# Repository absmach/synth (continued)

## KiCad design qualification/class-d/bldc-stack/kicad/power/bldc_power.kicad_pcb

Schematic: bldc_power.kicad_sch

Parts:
C_3V3: 100nF; C_0603_1608Metric; Voltage 16V
C_3V3_2: 10uF; C_1206_3216Metric; Voltage 16V
C_12B2B: 100nF; C_0603_1608Metric; Voltage 25V
C_BOOT_U: 100nF; C_0603_1608Metric; Voltage 50V
C_BOOT_V: 100nF; C_0603_1608Metric; Voltage 50V
C_BOOT_W: 100nF; C_0603_1608Metric; Voltage 50V
C_BUCK_BOOT: 100nF; C_0603_1608Metric; Voltage 16V
C_BUCK_FF: 100pF; C_0603_1608Metric; Voltage 16V
C_BUCK_IN: 10uF; C_1206_3216Metric; Voltage 50V
C_BUCK_IN2: 220nF; C_0603_1608Metric; Voltage 50V
C_BUCK_OUT1, C_BUCK_OUT2: 22uF; C_1206_3216Metric; Voltage 25V
C_BUCK_OUT3: 100nF; C_0603_1608Metric; Voltage 25V
C_BULK1, C_BULK2: 470uF; CP_Radial_D12.5mm_P5.00mm; Voltage 50V; MPN EEU-FR1H471; LCSC C1589760
C_CS_U_F: 100pF; C_0603_1608Metric; Voltage 16V
C_CS_U_IN: 100nF; C_0603_1608Metric; Voltage 16V
C_CS_V_F: 100pF; C_0603_1608Metric; Voltage 16V
C_CS_V_IN: 100nF; C_0603_1608Metric; Voltage 16V
C_CS_W_F: 100pF; C_0603_1608Metric; Voltage 16V
C_CS_W_IN: 100nF; C_0603_1608Metric; Voltage 16V
C_GD_BULK: 10uF; C_1206_3216Metric; Voltage 25V
C_GD_U: 100nF; C_0603_1608Metric; Voltage 25V
C_GD_V: 100nF; C_0603_1608Metric; Voltage 25V
C_GD_W: 100nF; C_0603_1608Metric; Voltage 25V
C_IN1, C_IN2: 10uF; C_1206_3216Metric; Voltage 50V
C_IN3: 100nF; C_0603_1608Metric; Voltage 50V
C_IS_OUT_U: 100nF; C_0603_1608Metric; Voltage 16V
C_IS_OUT_V: 100nF; C_0603_1608Metric; Voltage 16V
C_IS_OUT_W: 100nF; C_0603_1608Metric; Voltage 16V
C_REF: 100nF; C_0603_1608Metric; Voltage 16V
C_VBUS_S: 100nF; C_0603_1608Metric; Voltage 16V
D_BOOT_U: 1N5819HW; D_SOD-123; MPN 1N5819HW-7-F; LCSC C82544
D_BOOT_V: 1N5819HW; D_SOD-123; MPN 1N5819HW-7-F; LCSC C82544
D_BOOT_W: 1N5819HW; D_SOD-123; MPN 1N5819HW-7-F; LCSC C82544
D_REV_Z: 15V; D_SOD-123; MPN BZT52C15; LCSC C2104
D_TVS: SMBJ30A; D_SMB; MPN SMBJ30A
H1, H2, H3, H4: (no value); MountingHole_2.5mm
J_B2B: PWR; PinSocket_2x10_P2.54mm_Vertical; MPN 2.54-2*10P; LCSC C30867
J_MOTOR: MOTOR; TerminalBlock_Phoenix_MKDS-1,5-3-5.08_1x03_P5.08mm_Horizont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; MPN 1715734; LCSC C480520
J_PWR: 24V_IN; TerminalBlock_Phoenix_MKDS-1,5-2-5.08_1x02_P5.08mm_Horizont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; MPN 1715721; LCSC C480516
L_12B2B: 600ohm@100MHz; L_0603_1608Metric
L_BUCK: 6.8uH; L_Bourns_SRN6045TA; MPN SRN6045TA-6R8M
Q_FAULT: 2N3904; TO-92_Inline; MPN 2N3904; LCSC C20505
Q_GE: IRF4905; TO-220-3_Vertical; MPN IRF4905PBF; LCSC C2564
Q_GE_CTRL: 2N3904; TO-92_Inline; MPN 2N3904; LCSC C20505
Q_REV: IRF4905; TO-220-3_Vertical; MPN IRF4905PBF; LCSC C2564
Q_UH: 80V 100A; TDSON-8-1; MPN BSC030N08NS5ATMA1; LCSC C501507
Q_UL: 80V 100A; TDSON-8-1; MPN BSC030N08NS5ATMA1; LCSC C501507
Q_VH: 80V 100A; TDSON-8-1; MPN BSC030N08NS5ATMA1; LCSC C501507
Q_VL: 80V 100A; TDSON-8-1; MPN BSC030N08NS5ATMA1; LCSC C501507
Q_WH: 80V 100A; TDSON-8-1; MPN BSC030N08NS5ATMA1; LCSC C501507
Q_WL: 80V 100A; TDSON-8-1; MPN BSC030N08NS5ATMA1; LCSC C501507
R_BUCK_FB_B: 10k; R_0603_1608Metric; Tolerance 1%
R_BUCK_FB_T: 110k; R_0603_1608Metric; Tolerance 1%
R_BUCK_RT: 33k; R_0603_1608Metric; Tolerance 1%
R_CS_U_F: 39k; R_0603_1608Metric; Tolerance 1%
R_CS_U_G: 1k; R_0603_1608Metric; Tolerance 1%
R_CS_U_IN: 1k; R_0603_1608Metric; Tolerance 1%
R_CS_V_F: 39k; R_0603_1608Metric; Tolerance 1%
R_CS_V_G: 1k; R_0603_1608Metric; Tolerance 1%
R_CS_V_IN: 1k; R_0603_1608Metric; Tolerance 1%
R_CS_W_F: 39k; R_0603_1608Metric; Tolerance 1%
R_CS_W_G: 1k; R_0603_1608Metric; Tolerance 1%
R_CS_W_IN: 1k; R_0603_1608Metric; Tolerance 1%
R_FAULT_B: 10k; R_0603_1608Metric
R_FAULT_PU: 10k; R_0603_1608Metric
R_FAULT_SENSE: 1k; R_0603_1608Metric
R_GE_B: 10k; R_0603_1608Metric
R_GE_BD: 10k; R_0603_1608Metric
R_GE_PU: 10k; R_0603_1608Metric
R_GH_U: 10R; R_0603_1608Metric
R_GH_V: 10R; R_0603_1608Metric
R_GH_W: 10R; R_0603_1608Metric
R_GL_U: 10R; R_0603_1608Metric
R_GL_V: 10R; R_0603_1608Metric
R_GL_W: 10R; R_0603_1608Metric
R_GS_UH: 10k; R_0603_1608Metric
R_GS_UL: 10k; R_0603_1608Metric
R_GS_VH: 10k; R_0603_1608Metric
R_GS_VL: 10k; R_0603_1608Metric
R_GS_WH: 10k; R_0603_1608Metric
R_GS_WL: 10k; R_0603_1608Metric
R_HIN_U: 10k; R_0603_1608Metric
R_HIN_V: 10k; R_0603_1608Metric
R_HIN_W: 10k; R_0603_1608Metric
R_IS_OUT_U: 1k; R_0603_1608Metric
R_IS_OUT_V: 1k; R_0603_1608Metric
R_IS_OUT_W: 1k; R_0603_1608Metric
R_LIN_U: 10k; R_0603_1608Metric
R_LIN_V: 10k; R_0603_1608Metric
R_LIN_W: 10k; R_0603_1608Metric
R_REF_B: 10k; R_0603_1608Metric; Tolerance 1%
R_REF_T: 10k; R_0603_1608Metric; Tolerance 1%
R_REV_G1: 22k; R_0603_1608Metric
R_REV_G2: 10k; R_0603_1608Metric
R_SH_U: 5mR; R_2512_6332Metric; Tolerance 1%
R_SH_V: 5mR; R_2512_6332Metric; Tolerance 1%
R_SH_W: 5mR; R_2512_6332Metric; Tolerance 1%
R_VBUS_S1: 100k; R_0603_1608Metric; Tolerance 1%
R_VBUS_S2: 13k; R_0603_1608Metric; Tolerance 1%
U_BUCK: LMR38010; HSOP-8-1EP_3.9x4.9mm_P1.27mm_EP2.41x3.1mm; MPN LMR38010SDDAR
U_CS1, U_CS2: MCP6022; SOIC-8_3.9x4.9mm_P1.27mm; MPN MCP6022-I/SN; LCSC C34047
U_GD_U: IR2101; SOIC-8_3.9x4.9mm_P1.27mm; MPN IR2101STRPBF; LCSC C2956
U_GD_V: IR2101; SOIC-8_3.9x4.9mm_P1.27mm; MPN IR2101STRPBF; LCSC C2956
U_GD_W: IR2101; SOIC-8_3.9x4.9mm_P1.27mm; MPN IR2101STRPBF; LCSC C2956

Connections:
+3V3: C_3V3.1, C_3V3_2.1, J_B2B.13, R_FAULT_PU.1, R_REF_T.1, U_CS1.8 (V+), U_CS2.8 (V+)
+12V: C_BUCK_FF.1, C_BUCK_OUT1.1, C_BUCK_OUT2.1, C_BUCK_OUT3.1, L_12B2B.1, L_BUCK.2, Q_GE.3 (S), R_BUCK_FB_T.1, R_GE_PU.1
+12V_B2B: C_12B2B.1, J_B2B.14, L_12B2B.2
+12V_GD: C_GD_BULK.1, C_GD_U.1, C_GD_V.1, C_GD_W.1, D_BOOT_U.2 (A), D_BOOT_V.2 (A), D_BOOT_W.2 (A), Q_GE.2 (D), U_GD_U.1 (VCC), U_GD_V.1 (VCC), U_GD_W.1 (VCC)
+24V_IN: J_PWR.1, Q_REV.2 (D)
BOOT_BUCK: C_BUCK_BOOT.1, U_BUCK.7 (boot)
BOOT_U: C_BOOT_U.1, D_BOOT_U.1 (K), U_GD_U.8 (VB)
BOOT_V: C_BOOT_V.1, D_BOOT_V.1 (K), U_GD_V.8 (VB)
BOOT_W: C_BOOT_W.1, D_BOOT_W.1 (K), U_GD_W.8 (VB)
CS_U_FB: C_CS_U_F.2, R_CS_U_F.2, R_CS_U_G.1, U_CS1.2 (-)
CS_U_IN: C_CS_U_IN.1, R_CS_U_IN.2, U_CS1.3 (+)
CS_U_OUT: C_CS_U_F.1, R_CS_U_F.1, R_IS_OUT_U.1, U_CS1.1
CS_V_FB: C_CS_V_F.2, R_CS_V_F.2, R_CS_V_G.1, U_CS1.6 (-)
CS_V_IN: C_CS_V_IN.1, R_CS_V_IN.2, U_CS1.5 (+)
CS_V_OUT: C_CS_V_F.1, R_CS_V_F.1, R_IS_OUT_V.1, U_CS1.7
CS_W_FB: C_CS_W_F.2, R_CS_W_F.2, R_CS_W_G.1, U_CS2.2 (-)
CS_W_IN: C_CS_W_IN.1, R_CS_W_IN.2, U_CS2.3 (+)
CS_W_OUT: C_CS_W_F.1, R_CS_W_F.1, R_FAULT_SENSE.1, R_IS_OUT_W.1, U_CS2.1
FAULT_DRIVE: Q_FAULT.2 (B), R_FAULT_B.1, R_FAULT_B.2, U_CS2.7
FAULT_N: J_B2B.12, Q_FAULT.3 (C), R_FAULT_PU.2
FAULT_SENSE: R_FAULT_SENSE.2, U_CS2.5 (+)
FB_BUCK: C_BUCK_FF.2, R_BUCK_FB_B.1, R_BUCK_FB_T.2, U_BUCK.5 (fb)
GATE_EN: J_B2B.11, R_GE_B.1
GATE_REV: D_REV_Z.2 (A), Q_REV.1 (G), R_REV_G1.2, R_REV_G2.1
GE_DRIVE: Q_GE_CTRL.2 (B), R_GE_B.2, R_GE_BD.1
GE_GATE: Q_GE.1 (G), Q_GE_CTRL.3 (C), R_GE_PU.2
GH_U: Q_UH.4 (G), R_GH_U.1, R_GH_U.2, R_GS_UH.1, U_GD_U.7 (HO)
GH_V: Q_VH.4 (G), R_GH_V.1, R_GH_V.2, R_GS_VH.1, U_GD_V.7 (HO)
GH_W: Q_WH.4 (G), R_GH_W.1, R_GH_W.2, R_GS_WH.1, U_GD_W.7 (HO)
GL_U: Q_UL.4 (G), R_GL_U.1, R_GL_U.2, R_GS_UL.1, U_GD_U.5 (LO)
GL_V: Q_VL.4 (G), R_GL_V.1, R_GL_V.2, R_GS_VL.1, U_GD_V.5 (LO)
GL_W: Q_WL.4 (G), R_GL_W.1, R_GL_W.2, R_GS_WL.1, U_GD_W.5 (LO)
GND: C_3V3.2, C_3V3_2.2, C_12B2B.2, C_BUCK_IN.2, C_BUCK_IN2.2, C_BUCK_OUT1.2, C_BUCK_OUT2.2, C_BUCK_OUT3.2, C_BULK1.2, C_BULK2.2, C_CS_U_IN.2, C_CS_V_IN.2, C_CS_W_IN.2, C_GD_BULK.2, C_GD_U.2, C_GD_V.2, C_GD_W.2, C_IN1.2, C_IN2.2, C_IN3.2, C_IS_OUT_U.2, C_IS_OUT_V.2, C_IS_OUT_W.2, C_REF.2, D_TVS.2 (A), J_B2B.15, J_B2B.16, J_B2B.17, J_B2B.18, J_B2B.19, J_B2B.20, J_PWR.2, Q_FAULT.1 (E), Q_GE_CTRL.1 (E), R_BUCK_FB_B.2, R_BUCK_RT.2, R_CS_U_G.2, R_CS_V_G.2, R_CS_W_G.2, R_GE_BD.2, R_HIN_U.2, R_HIN_V.2, R_HIN_W.2, R_LIN_U.2, R_LIN_V.2, R_LIN_W.2, R_REF_B.2, R_REV_G2.2, R_SH_U.2, R_SH_V.2, R_SH_W.2, U_BUCK.1 (gnd), U_BUCK.9 (pad), U_CS1.4 (V-), U_CS2.4 (V-), U_GD_U.4 (COM), U_GD_V.4 (COM), U_GD_W.4 (COM)
ISENSE_U: C_IS_OUT_U.1, J_B2B.7, R_IS_OUT_U.2
ISENSE_V: C_IS_OUT_V.1, J_B2B.8, R_IS_OUT_V.2
ISENSE_W: C_IS_OUT_W.1, J_B2B.9, R_IS_OUT_W.2
PHASE_U: C_BOOT_U.2, J_MOTOR.1, Q_UH.1 (S), Q_UH.2 (S), Q_UH.3 (S), Q_UL.5 (D), R_GS_UH.2, U_GD_U.6 (VS)
PHASE_V: C_BOOT_V.2, J_MOTOR.2, Q_VH.1 (S), Q_VH.2 (S), Q_VH.3 (S), Q_VL.5 (D), R_GS_VH.2, U_GD_V.6 (VS)
PHASE_W: C_BOOT_W.2, J_MOTOR.3, Q_WH.1 (S), Q_WH.2 (S), Q_WH.3 (S), Q_WL.5 (D), R_GS_WH.2, U_GD_W.6 (VS)
PWM_UH: J_B2B.1, R_HIN_U.1, U_GD_U.2 (HIN)
PWM_UL: J_B2B.2, R_LIN_U.1, U_GD_U.3 (LIN)
PWM_VH: J_B2B.3, R_HIN_V.1, U_GD_V.2 (HIN)
PWM_VL: J_B2B.4, R_LIN_V.1, U_GD_V.3 (LIN)
PWM_WH: J_B2B.5, R_HIN_W.1, U_GD_W.2 (HIN)
PWM_WL: J_B2B.6, R_LIN_W.1, U_GD_W.3 (LIN)
RT_BUCK: R_BUCK_RT.1, U_BUCK.4 (rt_sync)
SHUNT_U: Q_UL.1 (S), Q_UL.2 (S), Q_UL.3 (S), R_CS_U_IN.1, R_GS_UL.2, R_SH_U.1
SHUNT_V: Q_VL.1 (S), Q_VL.2 (S), Q_VL.3 (S), R_CS_V_IN.1, R_GS_VL.2, R_SH_V.1
SHUNT_W: Q_WL.1 (S), Q_WL.2 (S), Q_WL.3 (S), R_CS_W_IN.1, R_GS_WL.2, R_SH_W.1
SW_BUCK: C_BUCK_BOOT.2, L_BUCK.1, U_BUCK.8 (sw)
VBUS: C_BUCK_IN.1, C_BUCK_IN2.1, C_BULK1.1, C_BULK2.1, C_IN1.1, C_IN2.1, C_IN3.1, D_REV_Z.1 (K), D_TVS.1 (K), Q_REV.3 (S), Q_UH.5 (D), Q_VH.5 (D), Q_WH.5 (D), R_REV_G1.1, R_VBUS_S1.1, U_BUCK.2 (en), U_BUCK.3 (vin)
VBUS_SENSE: C_VBUS_S.1, J_B2B.10, R_VBUS_S1.2, R_VBUS_S2.1
VREF: C_REF.1, R_REF_B.1, R_REF_T.2, U_CS2.6 (-)

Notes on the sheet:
MOUNTING
24V INPUT
3-PHASE BRIDGE
GATE DRIVE
CURRENT SENSE
12V BUCK
BUS SENSE
OVER-CURRENT FLAG
BOARD-TO-BOARD
J_PWR 1 = +24 V, 2 = GND. Q_REV is a P-FET reverse-polarity block:
drain to input, source to VBUS. R_REV_G1/G2 22k/10k hold VGS near -16.5 V
at 24 V; D_REV_Z clamps VGS at 15 V during a TVS clamp.
D_TVS SMBJ30A: VWM 30 V, VBR 33.3-36.8 V, clamp 48.4 V at 12.4 A.
C_BULK1/2 are 470 uF 50 V (24 V x 1.5 = 36 V minimum rating).
No fuse is fitted; the 24 V feed must be externally limited to 10 A.
BSC030N08NS5: 80 V, 100 A, 3.0 mOhm max at VGS 10 V, PG-TDSON-8.
Each half bridge has three source pins in parallel; the drain pad is pin 5.
Low-side shunt 5 mOhm: 50 mV at 10 A, 0.5 W in a 2512 (1 W part).
Phase copper is 2 mm wide on 2 oz outer layers; see NETLIST.md.
IR2101: VCC 12 V, COM GND, HIN/LIN 3.3 V logic, HO/LO through 10 R.
Bootstrap: 1N5819HW from +12V_GD to VB, 100 nF from VB to VS.
HIN and LIN have 10k pulldowns so a floating MCU keeps both outputs low.
Q_GE is a 12 V load switch for the drivers, controlled by GATE_EN:
Q_GE_CTRL pulls the P-FET gate low, R_GE_PU holds it off.
IR2101 logic: HIN and LIN high together turns both outputs off;
dead time is the MCU's responsibility and is not checked by Synth.
Non-inverting gain: 1 + 39k/1k = 40. 10 A x 5 mOhm = 50 mV -> 2.0 V.
MCP6022 GBW 10 MHz, so the closed-loop band is about 250 kHz.
1k + 100 nF at the + input gives fc = 1.6 kHz; the 100 pF across
39k adds a 41 kHz pole, above the current-loop bandwidth.
The spare MCP6022 channel compares ISENSE_W with 1.65 V (about 8.25 A)
and pulls FAULT_N low through Q_FAULT.
LMR38010 (85 V absolute maximum, above the 48.4 V TVS clamp), 1 A.
Vout = 1.0 V x (1 + 110k/10k) = 12.0 V.
R_RT 33k sets 800 kHz; L 6.8 uH keeps the ripple below 0.3 A at 12 V/1 A.
L_12B2B isolates the board-to-board 12 V pin from the buck output.
VBUS divider: 24 x 13/113 = 2.76 V; 26.4 V gives 3.04 V.
This is the only 24 V signal leaving the power board.
Reference: 3.3 V x 10k/(10k+10k) = 1.65 V, about 8.25 A on the 5 mOhm shunt.
U_CS2 channel B output high on overcurrent -> Q_FAULT pulls FAULT_N low.

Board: 4 copper layers, 111 parts (0 on the bottom side), 53 nets, no tracks yet.

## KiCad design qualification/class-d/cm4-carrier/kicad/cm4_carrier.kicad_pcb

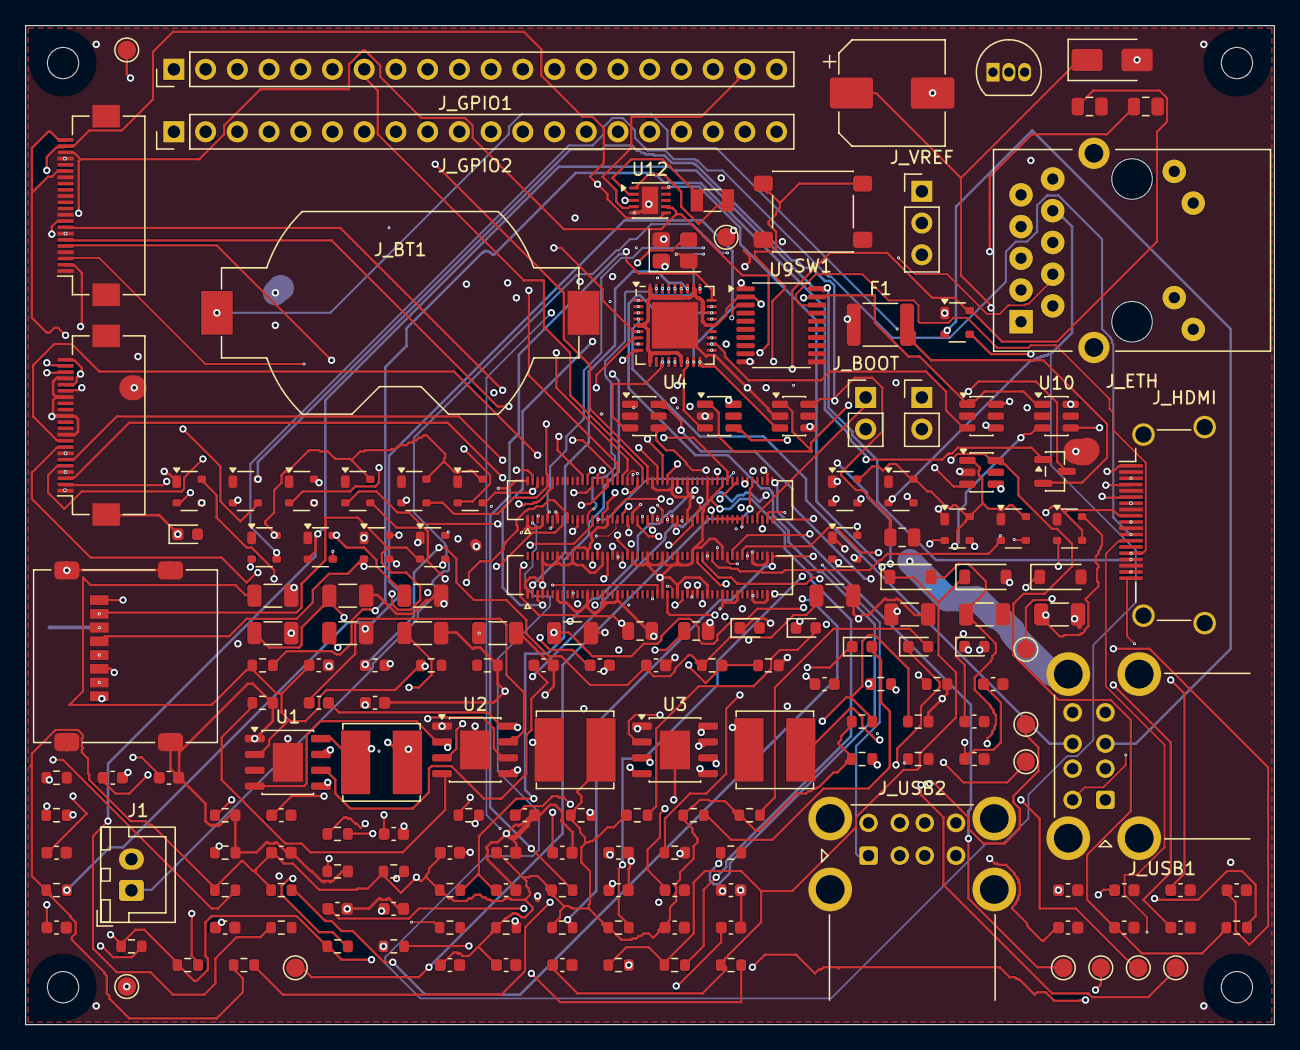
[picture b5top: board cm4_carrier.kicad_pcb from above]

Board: 6 copper layers, 100.0 x 80.0 mm, 184 parts (0 on the bottom side), 158 nets.

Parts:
C1: 47uF; CP_Elec_8x10
C2: 10uF; C_1206_3216Metric
C3: 220nF; C_0603_1608Metric
C_AUX: 10uF; C_1206_3216Metric
C_BOOT, C_BOOT2, C_BOOT3: 100nF; C_0603_1608Metric
C_CAM: 100nF; C_0603_1608Metric
C_CRFILT: 100nF; C_0603_1608Metric
C_CT1, C_CT2, C_CT3, C_CT4: 1nF; C_0603_1608Metric
C_DSI: 100nF; C_0603_1608Metric
C_FF, C_FF3: 100pF; C_0603_1608Metric
C_FF2: 56pF; C_0603_1608Metric
C_GEN: 100nF; C_0603_1608Metric
C_HDMI1: 1uF; C_0805_2012Metric
C_HDMI2: 100nF; C_0603_1608Metric
C_HDMI_CT: 1nF; C_0603_1608Metric
C_HDMI_VCCA: 100nF; C_0603_1608Metric
C_HDMI_VCCB: 100nF; C_0603_1608Metric
C_HUB1, C_HUB2, C_HUB3: 100nF; C_0603_1608Metric
C_HUB4: 10uF; C_1206_3216Metric
C_IN2_1, C_IN3_1: 10uF; C_1206_3216Metric
C_IN2_2, C_IN3_2: 220nF; C_0603_1608Metric
C_OUT1, C_OUT2, C_OUT4, C_OUT5, C_OUT7, C_OUT8: 22uF; C_1206_3216Metric
C_OUT3, C_OUT6, C_OUT9: 100nF; C_0603_1608Metric
C_PLLFILT: 100nF; C_0603_1608Metric
C_RESET: 1uF; C_0603_1608Metric
C_RTC: 100nF; C_0603_1608Metric
C_SD1: 10uF; C_1206_3216Metric
C_SD2: 100nF; C_0603_1608Metric
C_SD_CT: 1nF; C_0603_1608Metric
C_SD_IN: 100nF; C_0603_1608Metric
C_TCT: 100nF; C_0603_1608Metric
C_USB1, C_USB2, C_USB3, C_USB4: 1uF; C_0805_2012Metric
C_USB1B, C_USB2B, C_USB3B, C_USB4B: 100nF; C_0603_1608Metric
C_VCC: 1uF; C_0603_1608Metric
C_X1, C_X2: 18pF; C_0603_1608Metric
D1: SMAJ15A; D_SMA
D_3V3: 3V3; LED_0603_1608Metric
D_ACT: ACT; LED_0603_1608Metric
D_ETH: ETH_ACT; LED_0603_1608Metric
D_ETH2: ETH_SPD; LED_0603_1608Metric
D_ETH_ESD1, D_ETH_ESD2, D_ETH_ESD3, D_ETH_ESD4: TVS; SOT-143
D_FAN: FLYBACK; D_SOD-123
D_HDMI1, D_HDMI2, D_HDMI3, D_HDMI4, D_HDMI5: TVS; SOT-143
D_PWR: 5V; LED_0603_1608Metric
D_PWR_CM4: PWR; LED_0603_1608Metric
D_RTC1: 3V3; D_SOD-123
D_RTC2: BAT; D_SOD-123
D_SD1, D_SD2, D_SD3: TVS; SOT-143
D_USB1, D_USB2, D_USB3, D_USB4: TVS; SOT-143
D_USB_UP: TVS; SOT-143
F1: 2.6A_PTC; Fuse_1812_4532Metric
H1, H2, H3, H4: M2.5; MountingHole_2.5mm
J1: 12V_IN; JST_XH_B2B-XH-A_1x02_P2.50mm_Vertical
J_BOOT: nRPIBOOT; PinHeader_1x02_P2.54mm_Vertical
J_BT1: CR2032; BatteryHolder_Keystone_1058_1x2032
J_CAM: CSI0; Hirose_FH12-22S-0.5SH_1x22-1MP_P0.50mm_Horizontal
J_CM4A: CM4_A; Hirose_DF40C-100DS-0.4V_2x50_P0.4mm
J_CM4B: CM4_B; Hirose_DF40C-100DS-0.4V_2x50_P0.4mm
J_DSI: DSI0; Hirose_FH12-22S-0.5SH_1x22-1MP_P0.50mm_Horizontal
J_ETH: GbE; RJ45_UDE_RB1-125B8G1A
J_FAN: FAN; PinHeader_1x02_P2.54mm_Vertical
J_GPIO1: GPIO_ODD; PinHeader_1x20_P2.54mm_Vertical
J_GPIO2: GPIO_EVEN; PinHeader_1x20_P2.54mm_Vertical
J_HDMI: HDMI0; HDMI_A_Amphenol_10029449-x01xLF_Horizontal
J_SD: microSD; microSD_HC_Molex_47219-2001
J_USB1: USB1_2; USB_A_CUI_UJ2-ADH-TH_Horizontal_Stacked
J_USB2: USB3_4; USB_A_CUI_UJ2-ADH-TH_Horizontal_Stacked
J_VREF: VREF_SEL; PinHeader_1x03_P2.54mm_Vertical
L1, L2, L3: 6.8uH; L_Bourns_SRN6045TA
L_FB1: 600R; L_0603_1608Metric
Q1: DMP3098L; SOT-23
Q_LED: 2N7000; TO-92_Inline
R_3V3: 470; R_0603_1608Metric
R_ACT: 470; R_0603_1608Metric
R_CFG0, R_CFG1: 10k; R_0603_1608Metric
R_ETH, R_ETH2: 470; R_0603_1608Metric
R_FB2_B: 43.2k; R_0603_1608Metric
R_FB2_T, R_FB3_T: 100k; R_0603_1608Metric
R_FB3_B: 125k; R_0603_1608Metric
R_FB_B: 24.9k; R_0603_1608Metric
R_FB_T: 100k; R_0603_1608Metric
R_G1: 100k; R_0603_1608Metric
R_GEN: 100k; R_0603_1608Metric
R_HDMI_SCL: 2.2k; R_0603_1608Metric
R_HDMI_SCL_MCU: 2.2k; R_0603_1608Metric
R_HDMI_SDA: 2.2k; R_0603_1608Metric
R_HDMI_SDA_MCU: 2.2k; R_0603_1608Metric
R_LED_PWR: 470; R_0603_1608Metric
R_LOCAL: 10k; R_0603_1608Metric
R_OCS1, R_OCS2, R_OCS3, R_OCS4: 10k; R_0603_1608Metric
R_OE: 10k; R_0603_1608Metric
R_PG, R_PG2, R_PG3: 100k; R_0603_1608Metric
R_PWR: 470; R_0603_1608Metric
R_RBIAS: 12k; R_0603_1608Metric
R_RESET: 10k; R_0603_1608Metric
R_RT2, R_RT3: 33k; R_0603_1608Metric
R_RTC_INT: 10k; R_0603_1608Metric
R_RTC_SCL: 10k; R_0603_1608Metric
R_RTC_SDA: 10k; R_0603_1608Metric
R_SD_CMD: 10k; R_0603_1608Metric
R_SD_DAT0, R_SD_DAT1, R_SD_DAT2, R_SD_DAT3: 10k; R_0603_1608Metric
R_SD_PWR: 100k; R_0603_1608Metric
R_UV_B: 10k; R_0603_1608Metric
R_UV_T: 63.4k; R_0603_1608Metric
R_VBUS: 10k; R_0603_1608Metric
SW1: GLOBAL_EN; SW_SPST_PTS645Sx43SMTR92
TP_1V8: 1V8; TestPoint_Pad_D1.5mm
TP_3V3: 3V3; TestPoint_Pad_D1.5mm
TP_5V: 5V; TestPoint_Pad_D1.5mm
TP_CM4_1V8: CM4_1V8; TestPoint_Pad_D1.5mm
TP_CM4_3V3: CM4_3V3; TestPoint_Pad_D1.5mm
TP_GLOBAL_EN: GLOBAL_EN; TestPoint_Pad_D1.5mm
TP_NEXTRST: nEXTRST; TestPoint_Pad_D1.5mm
TP_PG1V8: PG_1V8; TestPoint_Pad_D1.5mm
TP_PG3V3: PG_3V3; TestPoint_Pad_D1.5mm
TP_PG5V: PG_5V; TestPoint_Pad_D1.5mm
TP_RUN_PG: RUN_PG; TestPoint_Pad_D1.5mm
U1: LMR33640; HSOP-8-1EP_3.9x4.9mm_P1.27mm_EP2.41x3.1mm
U2, U3: LMR38010; HSOP-8-1EP_3.9x4.9mm_P1.27mm_EP2.41x3.1mm
U4: USB2514B; QFN-36-1EP_6x6mm_P0.5mm_EP3.7x3.7mm
U5: USB1_PWR; SOT-23-6
U6: USB2_PWR; SOT-23-6
U7: USB3_PWR; SOT-23-6
U8: USB4_PWR; SOT-23-6
U9: TXS0108E; TSSOP-20_4.4x6.5mm_P0.65mm
U10: HDMI_5V; SOT-23-6
U11: SD_PWR; SOT-23-6
U12: PCF85063A; DFN-10-1EP_2.6x2.6mm_P0.5mm_EP1.3x2.2mm
Y1: 24MHz; Crystal_SMD_3225-4Pin_3.2x2.5mm
Y2: 32.768kHz; Crystal_SMD_3215-2Pin_3.2x1.5mm

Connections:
+1V8: C_OUT7.1, C_OUT8.1, C_OUT9.1, J_VREF.3, L3.2, R_FB3_T.1, R_PG3.1, TP_1V8.1
+3V3: C_CAM.1, C_DSI.1, C_HDMI_VCCA.1, C_HUB1.1, C_HUB2.1, C_HUB3.1, C_HUB4.1, C_OUT4.1, C_OUT5.1, C_OUT6.1, C_SD_IN.1, D_ETH_ESD1.4, D_ETH_ESD2.4, D_ETH_ESD3.4, D_ETH_ESD4.4, D_HDMI1.4, D_HDMI2.4, D_HDMI3.4, D_HDMI4.4, D_RTC1.2, D_USB_UP.4, J_CAM.18, J_CAM.22, J_DSI.17, J_DSI.22, J_GPIO1.1, J_GPIO1.9, J_VREF.1, L2.2, R_3V3.1, R_ACT.1, R_ETH.1, R_ETH2.1, R_FB2_T.1, R_GEN.1, R_HDMI_SCL_MCU.1, R_HDMI_SDA_MCU.1, R_LED_PWR.1, R_OCS1.1, R_OCS2.1, R_OCS3.1, R_OCS4.1, R_OE.1, R_PG2.1, R_RESET.1, R_SD_PWR.1, R_VBUS.1, TP_3V3.1, U4.5, U4.10, U4.15, U4.23, U4.29, U4.36, U9.2, U10.3, U11.1
+5V: C_HDMI_VCCB.1, C_OUT1.1, C_OUT2.1, C_OUT3.1, D_FAN.1, D_HDMI5.4, J_CM4A.77, J_CM4A.79, J_CM4A.81, J_CM4A.83, J_CM4A.85, J_CM4A.87, J_FAN.1, J_GPIO2.1, J_GPIO2.2, L1.2, L_FB1.1, R_FB_T.1, R_PG.1, R_PWR.1, TP_5V.1, U5.1, U6.1, U7.1, U8.1, U9.19, U10.1
+5V_AUX: C_AUX.1, C_IN2_1.1, C_IN2_2.1, C_IN3_1.1, C_IN3_2.1, L_FB1.2, U2.3, U3.3
BOOT_1V8: C_BOOT3.1, U3.7
BOOT_3V3: C_BOOT2.1, U2.7
BOOT_5V: C_BOOT.1, U1.7
CAM_CK_N: J_CAM.8, J_CM4B.40
CAM_CK_P: J_CAM.9, J_CM4B.42
CAM_D0_N: J_CAM.2, J_CM4B.28
CAM_D0_P: J_CAM.3, J_CM4B.30
CAM_D1_N: J_CAM.5, J_CM4B.34
CAM_D1_P: J_CAM.6, J_CM4B.36
CAM_GPIO: J_CAM.17, J_CM4A.97
CM4_1V8: J_CM4A.88, J_CM4A.90, TP_CM4_1V8.1
CM4_3V3: J_CM4A.84, J_CM4A.86, TP_CM4_3V3.1
DSI_CK_N: J_CM4B.69, J_DSI.8
DSI_CK_P: J_CM4B.71, J_DSI.9
DSI_D0_N: J_CM4B.57, J_DSI.2
DSI_D0_P: J_CM4B.59, J_DSI.3
DSI_D1_N: J_CM4B.63, J_DSI.5
DSI_D1_P: J_CM4B.65, J_DSI.6
ETH0_N: D_ETH_ESD1.3, J_CM4A.10, J_ETH.R3
ETH0_P: D_ETH_ESD1.2, J_CM4A.12, J_ETH.R2
ETH1_N: D_ETH_ESD2.3, J_CM4A.6, J_ETH.R5
ETH1_P: D_ETH_ESD2.2, J_CM4A.4, J_ETH.R4
ETH2_N: D_ETH_ESD3.3, J_CM4A.9, J_ETH.R7
ETH2_P: D_ETH_ESD3.2, J_CM4A.11, J_ETH.R6
ETH3_N: D_ETH_ESD4.3, J_CM4A.5, J_ETH.R9
ETH3_P: D_ETH_ESD4.2, J_CM4A.3, J_ETH.R8
ETH_LED_ACT: D_ETH.1, J_CM4A.15
ETH_LED_SPD: D_ETH2.1, J_CM4A.17
ETH_TCT: C_TCT.1, J_ETH.R1
FB_1V8: C_FF3.1, R_FB3_B.1, R_FB3_T.2, U3.5
FB_3V3: C_FF2.1, R_FB2_B.1, R_FB2_T.2, U2.5
FB_5V: C_FF.1, R_FB_B.1, R_FB_T.2, U1.5
GLOBAL_EN: C_GEN.1, J_CM4A.99, R_GEN.2, SW1.1, TP_GLOBAL_EN.1
GND: C1.2, C2.2, C3.2, C_AUX.2, C_CAM.2, C_CRFILT.2, C_CT1.2, C_CT2.2, C_CT3.2, C_CT4.2, C_DSI.2, C_GEN.2, C_HDMI1.2, C_HDMI2.2, C_HDMI_CT.2, C_HDMI_VCCA.2, C_HDMI_VCCB.2, C_HUB1.2, C_HUB2.2, C_HUB3.2, C_HUB4.2, C_IN2_1.2, C_IN2_2.2, C_IN3_1.2, C_IN3_2.2, C_OUT1.2, C_OUT2.2, C_OUT3.2, C_OUT4.2, C_OUT5.2, C_OUT6.2, C_OUT7.2, C_OUT8.2, C_OUT9.2, C_PLLFILT.2, C_RESET.2, C_RTC.2, C_SD1.2, C_SD2.2, C_SD_CT.2, C_SD_IN.2, C_TCT.2, C_USB1.2, C_USB1B.2, C_USB2.2, C_USB2B.2, C_USB3.2, C_USB3B.2, C_USB4.2, C_USB4B.2, C_VCC.2, C_X1.2, C_X2.2, D1.2, D_3V3.1, D_ETH_ESD1.1, D_ETH_ESD2.1, D_ETH_ESD3.1, D_ETH_ESD4.1, D_FAN.2, D_HDMI1.1, D_HDMI2.1, D_HDMI3.1, D_HDMI4.1, D_HDMI5.1, D_PWR.1, D_SD1.1, D_SD2.1, D_SD3.1, D_USB1.1, D_USB2.1, D_USB3.1, D_USB4.1, D_USB_UP.1, J1.2, J_BOOT.2, J_BT1.2, J_CAM.1, J_CAM.4, J_CAM.7, J_CAM.10, J_CAM.13, J_CAM.16, J_CAM.19, J_CAM.MP, J_CM4A.1, J_CM4A.2, J_CM4A.7, J_CM4A.8, J_CM4A.13, J_CM4A.14, J_CM4A.22, J_CM4A.23, J_CM4A.32, J_CM4A.33, J_CM4A.42, J_CM4A.43, J_CM4A.52, J_CM4A.53, J_CM4A.59, J_CM4A.60, J_CM4A.65, J_CM4A.66, J_CM4A.71, J_CM4A.74, J_CM4A.98, J_CM4B.1, J_CM4B.7, J_CM4B.8, J_CM4B.13, J_CM4B.14, J_CM4B.19, J_CM4B.20, J_CM4B.25, J_CM4B.26, J_CM4B.31, J_CM4B.32, J_CM4B.37, J_CM4B.38, J_CM4B.44, J_CM4B.50, J_CM4B.55, J_CM4B.56, J_CM4B.61, J_CM4B.62, J_CM4B.67, J_CM4B.68, J_CM4B.73, J_CM4B.74, J_CM4B.79, J_CM4B.80, J_CM4B.85, J_CM4B.86, J_CM4B.91, J_CM4B.92, J_CM4B.97, J_CM4B.98, J_DSI.1, J_DSI.4, J_DSI.7, J_DSI.10, J_DSI.13, J_DSI.16, J_DSI.19, J_DSI.MP, J_ETH.R10, J_ETH.SH, J_FAN.2, J_GPIO1.5, J_GPIO1.13, J_GPIO1.20, J_GPIO2.3, J_GPIO2.7, J_GPIO2.10, J_GPIO2.15, J_GPIO2.17, J_HDMI.2, J_HDMI.5, J_HDMI.8, J_HDMI.11, J_HDMI.17, J_HDMI.SH, J_SD.6, J_SD.SH, J_USB1.4, J_USB1.8, J_USB1.SH, J_USB2.4, J_USB2.8, J_USB2.SH, Q_LED.1, R_3V3.2, R_CFG0.2, R_CFG1.2, R_FB2_B.2, R_FB3_B.2, R_FB_B.2, R_LOCAL.2, R_PWR.2, R_RBIAS.2, R_RT2.2, R_RT3.2, R_UV_B.2, SW1.2, U1.1, U1.9, U2.1, U2.9, U3.1, U3.9, U4.37, U5.2, U6.2, U7.2, U8.2, U9.11, U10.2, U11.2, U12.5, U12.11, Y1.2, Y1.4
GPIO2: J_CM4A.58, J_GPIO1.2
GPIO3: J_CM4A.56, J_GPIO1.3
GPIO4: J_CM4A.54, J_GPIO1.4
GPIO5: J_CM4A.34, J_GPIO1.15
GPIO6: J_CM4A.30, J_GPIO1.16
GPIO7: J_CM4A.37, J_GPIO2.13
GPIO8: J_CM4A.39, J_GPIO2.12
GPIO9: J_CM4A.40, J_GPIO1.11
GPIO10: J_CM4A.44, J_GPIO1.10
GPIO11: J_CM4A.38, J_GPIO1.12
GPIO12: J_CM4A.31, J_GPIO2.16
GPIO13: J_CM4A.28, J_GPIO1.17
GPIO14: J_CM4A.55, J_GPIO2.4
GPIO15: J_CM4A.51, J_GPIO2.5
GPIO16: J_CM4A.29, J_GPIO2.18
GPIO17: J_CM4A.50, J_GPIO1.6
GPIO18: J_CM4A.49, J_GPIO2.6
GPIO19: J_CM4A.26, J_GPIO1.18
GPIO20: J_CM4A.27, J_GPIO2.19
GPIO21: J_CM4A.25, J_GPIO2.20
GPIO22: J_CM4A.46, J_GPIO1.8
GPIO23: J_CM4A.47, J_GPIO2.8
GPIO24: J_CM4A.45, J_GPIO2.9
GPIO25: J_CM4A.41, J_GPIO2.11
GPIO26: J_CM4A.24, J_GPIO1.19, R_RTC_INT.2, U12.4
GPIO27: J_CM4A.48, J_GPIO1.7
GPIO_VREF: J_CM4A.78, J_VREF.2
HDMI_5V: C_HDMI1.1, C_HDMI2.1, J_HDMI.18, U10.6
HDMI_CEC: J_CM4B.51, J_HDMI.13
HDMI_CK_N: D_HDMI4.3, J_CM4B.90, J_HDMI.12
HDMI_CK_P: D_HDMI4.2, J_CM4B.88, J_HDMI.10
HDMI_CT: C_HDMI_CT.1, U10.4
HDMI_D0_N: D_HDMI3.3, J_CM4B.84, J_HDMI.9
HDMI_D0_P: D_HDMI3.2, J_CM4B.82, J_HDMI.7
HDMI_D1_N: D_HDMI2.3, J_CM4B.78, J_HDMI.6
HDMI_D1_P: D_HDMI2.2, J_CM4B.76, J_HDMI.4
HDMI_D2_N: D_HDMI1.3, J_CM4B.72, J_HDMI.3
HDMI_D2_P: D_HDMI1.2, J_CM4B.70, J_HDMI.1
HDMI_HPD: J_CM4B.53, J_HDMI.19
HDMI_OE: R_OE.2, U9.10
HDMI_SCL_CONN: D_HDMI5.3, J_HDMI.15, R_HDMI_SCL.1, U9.18
HDMI_SCL_MCU: J_CM4B.100, R_HDMI_SCL_MCU.2, U9.3
HDMI_SDA_CONN: D_HDMI5.2, J_HDMI.16, R_HDMI_SDA.1, U9.20
HDMI_SDA_MCU: J_CM4B.99, R_HDMI_SDA_MCU.2, U9.1
HUB_CFG0: R_CFG0.1, U4.24
HUB_CFG1: R_CFG1.1, U4.25
HUB_CRFILT: C_CRFILT.1, U4.14
HUB_LOCAL: R_LOCAL.1, U4.28
HUB_OCS1: R_OCS1.2, U4.13
HUB_OCS2: R_OCS2.2, U4.17
HUB_OCS3: R_OCS3.2, U4.19
HUB_OCS4: R_OCS4.2, U4.21
HUB_PLLFILT: C_PLLFILT.1, U4.34
HUB_RBIAS: R_RBIAS.1, U4.35
HUB_RESET: C_RESET.1, R_RESET.2, U4.26
HUB_VBUS_DET: R_VBUS.2, U4.27
HUB_XTAL1: C_X1.1, U4.33, Y1.1
HUB_XTAL2: C_X2.1, U4.32, Y1.3
ID_SC: J_CM4A.35, J_GPIO2.14
ID_SD: J_CM4A.36, J_GPIO1.14
LED_ACT_A: D_ACT.2, R_ACT.2
LED_ETH2_A: D_ETH2.2, R_ETH2.2
LED_ETH_A: D_ETH.2, R_ETH.2
LED_PWR_CM4: D_PWR_CM4.1, Q_LED.3
LED_PWR_CM4_A: D_PWR_CM4.2, R_LED_PWR.2
NEXTRST: J_CM4A.100, TP_NEXTRST.1
NRPIBOOT: J_BOOT.1, J_CM4A.93
PG_1V8: R_PG3.2, TP_PG1V8.1, U3.6
PG_3V3: R_PG2.2, TP_PG3V3.1, U2.6, U3.2
PG_5V: R_PG.2, TP_PG5V.1, U1.4, U2.2
PI_LED_ACT: D_ACT.1, J_CM4A.21
PI_LED_NPWR: J_CM4A.95, Q_LED.2
RTC_BAT: D_RTC2.2, J_BT1.1
RTC_OSC1: U12.1, Y2.1
RTC_OSC2: U12.2, Y2.2
RTC_VDD: C_RTC.1, D_RTC1.1, D_RTC2.1, R_RTC_INT.1, R_RTC_SCL.1, R_RTC_SDA.1, U12.3, U12.10
RT_1V8: R_RT3.1, U3.4
RT_3V3: R_RT2.1, U2.4
RUN_PG: J_CM4A.92, TP_RUN_PG.1
SCL0: J_CAM.20, J_CM4A.80, J_DSI.20, R_RTC_SCL.2, U12.7
SDA0: J_CAM.21, J_CM4A.82, J_DSI.21, R_RTC_SDA.2, U12.6
SD_CLK: D_SD1.2, J_CM4A.57, J_SD.5
SD_CMD: D_SD1.3, J_CM4A.62, J_SD.3, R_SD_CMD.2
SD_CT: C_SD_CT.1, U11.4
SD_DAT0: D_SD2.2, J_CM4A.63, J_SD.7, R_SD_DAT0.2
SD_DAT1: D_SD2.3, J_CM4A.67, J_SD.8, R_SD_DAT1.2
SD_DAT2: D_SD3.2, J_CM4A.69, J_SD.1, R_SD_DAT2.2
SD_DAT3: D_SD3.3, J_CM4A.61, J_SD.2, R_SD_DAT3.2
SD_PWR_ON: J_CM4A.75, R_SD_PWR.2, U11.3
SD_VDD: C_SD1.1, C_SD2.1, D_SD1.4, D_SD2.4, D_SD3.4, J_SD.4, R_SD_CMD.1, R_SD_DAT0.1, R_SD_DAT1.1, R_SD_DAT2.1, R_SD_DAT3.1, U11.6
SW_1V8: C_BOOT3.2, L3.1, U3.8
SW_3V3: C_BOOT2.2, L2.1, U2.8
SW_5V: C_BOOT.2, L1.1, U1.8
USB1_N: D_USB1.3, J_USB1.2, U4.1
USB1_P: D_USB1.2, J_USB1.3, U4.2
USB2_N: D_USB2.3, J_USB1.6, U4.3
USB2_P: D_USB2.2, J_USB1.7, U4.4
USB3_N: D_USB3.3, J_USB2.2, U4.6
USB3_P: D_USB3.2, J_USB2.3, U4.7
USB4_N: D_USB4.3, J_USB2.6, U4.8
USB4_P: D_USB4.2, J_USB2.7, U4.9
USB_CT1: C_CT1.1, U5.4
USB_CT2: C_CT2.1, U6.4
USB_CT3: C_CT3.1, U7.4
USB_CT4: C_CT4.1, U8.4
USB_ON1: U4.12, U5.3
USB_ON2: U4.16, U6.3
USB_ON3: U4.18, U7.3
USB_ON4: U4.20, U8.3
USB_UP_N: D_USB_UP.3, J_CM4B.3, U4.30
USB_UP_P: D_USB_UP.2, J_CM4B.5, U4.31
USB_VBUS1: C_USB1.1, C_USB1B.1, D_USB1.4, J_USB1.1, U5.6
USB_VBUS2: C_USB2.1, C_USB2B.1, D_USB2.4, J_USB1.5, U6.6
USB_VBUS3: C_USB3.1, C_USB3B.1, D_USB3.4, J_USB2.1, U7.6
USB_VBUS4: C_USB4.1, C_USB4B.1, D_USB4.4, J_USB2.5, U8.6
VCC_5V: C_VCC.1, U1.6
VIN_12V: F1.1, J1.1
VIN_FUSED: F1.2, Q1.2
VIN_GATE: Q1.1, R_G1.2
VIN_PROT: C1.1, C2.1, C3.1, D1.1, Q1.3, R_G1.1, R_UV_T.1, U1.2
